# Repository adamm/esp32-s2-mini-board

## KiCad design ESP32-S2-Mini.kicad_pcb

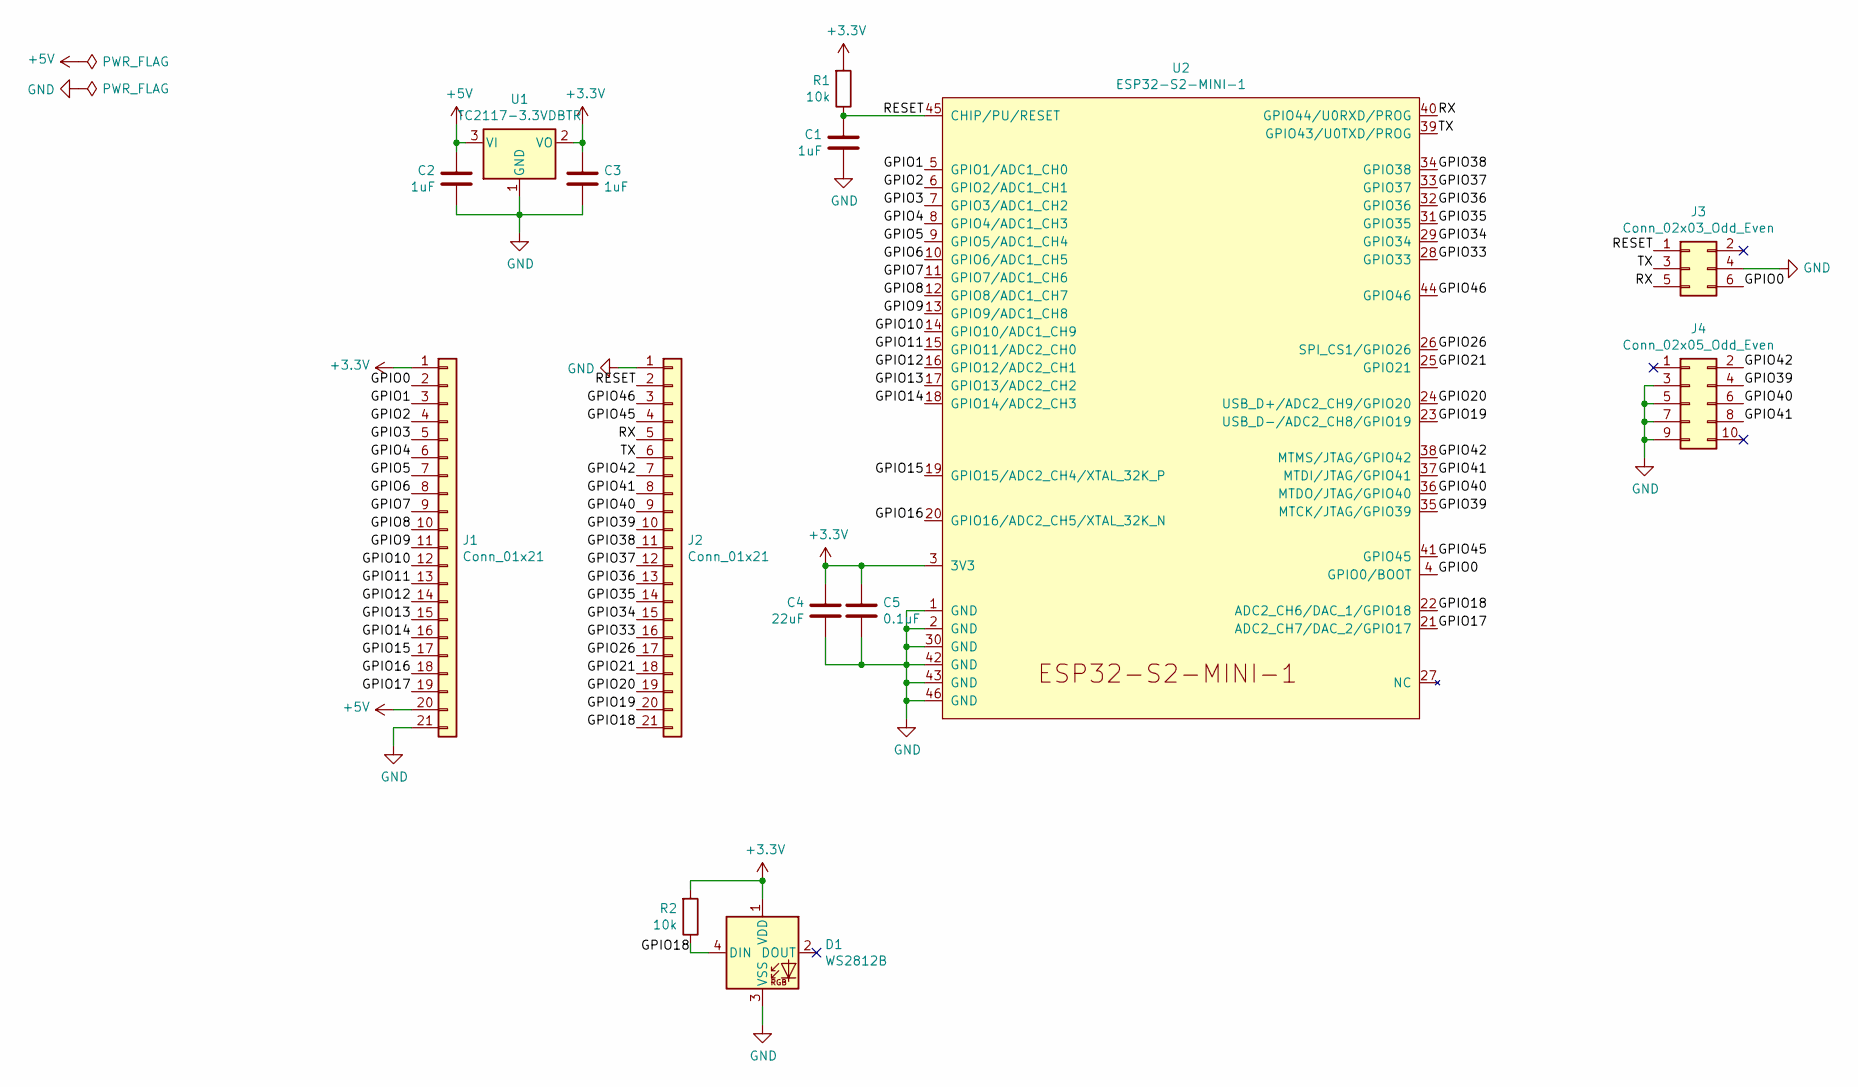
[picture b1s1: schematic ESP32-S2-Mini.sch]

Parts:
C1, C2, C3: 1uF; C_0805_2012Metric
C4: 22uF; C_0805_2012Metric
C5: 0.1uF; C_0805_2012Metric
D1: WS2812B; LED_WS2812B_PLCC4_5.0x5.0mm_P3.2mm
J1, J2: Conn_01x21; PinHeader_1x21_P2.54mm_Vertical
J3: Conn_02x03_Odd_Even; IDC-Header_2x03_P2.54mm_Vertical
J4: Conn_02x05_Odd_Even; IDC-Header_2x05_P2.54mm_Vertical
R1, R2: 10k; R_0805_2012Metric
U1: TC2117-3.3VDBTR; SOT-223-3_TabPin2
U2: ESP32-S2-MINI-1

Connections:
+3V3: C3.1, C4.2, C5.1, D1.1 (VDD), J1.1, R1.2, R2.2, U1.2 (VO), U2.3 (3V3)
+5V: C2.2, J1.20, U1.3 (VI)
/GPIO0: J1.2, J3.6, U2.4 (GPIO0/BOOT)
/GPIO1: J1.3, U2.5 (GPIO1/ADC1_CH0)
/GPIO2: J1.4, U2.6 (GPIO2/ADC1_CH1)
/GPIO3: J1.5, U2.7 (GPIO3/ADC1_CH2)
/GPIO4: J1.6, U2.8 (GPIO4/ADC1_CH3)
/GPIO5: J1.7, U2.9 (GPIO5/ADC1_CH4)
/GPIO6: J1.8, U2.10 (GPIO6/ADC1_CH5)
/GPIO7: J1.9, U2.11 (GPIO7/ADC1_CH6)
/GPIO8: J1.10, U2.12 (GPIO8/ADC1_CH7)
/GPIO9: J1.11, U2.13 (GPIO9/ADC1_CH8)
/GPIO10: J1.12, U2.14 (GPIO10/ADC1_CH9)
/GPIO11: J1.13, U2.15 (GPIO11/ADC2_CH0)
/GPIO12: J1.14, U2.16 (GPIO12/ADC2_CH1)
/GPIO13: J1.15, U2.17 (GPIO13/ADC2_CH2)
/GPIO14: J1.16, U2.18 (GPIO14/ADC2_CH3)
/GPIO15: J1.17, U2.19 (GPIO15/ADC2_CH4/XTAL_32K_P)
/GPIO16: J1.18, U2.20 (GPIO16/ADC2_CH5/XTAL_32K_N)
/GPIO17: J1.19, U2.21 (ADC2_CH7/DAC_2/GPIO17)
/GPIO18: D1.4 (DIN), J2.21, R2.1, U2.22 (ADC2_CH6/DAC_1/GPIO18)
/GPIO19: J2.20, U2.23 (USB_D-/ADC2_CH8/GPIO19)
/GPIO20: J2.19, U2.24 (USB_D+/ADC2_CH9/GPIO20)
/GPIO21: J2.18, U2.25 (GPIO21)
/GPIO26: J2.17, U2.26 (SPI_CS1/GPIO26)
/GPIO33: J2.16, U2.28 (GPIO33)
/GPIO34: J2.15, U2.29 (GPIO34)
/GPIO35: J2.14, U2.31 (GPIO35)
/GPIO36: J2.13, U2.32 (GPIO36)
/GPIO37: J2.12, U2.33 (GPIO37)
/GPIO38: J2.11, U2.34 (GPIO38)
/GPIO39: J2.10, J4.4, U2.35 (MTCK/JTAG/GPIO39)
/GPIO40: J2.9, J4.6, U2.36 (MTDO/JTAG/GPIO40)
/GPIO41: J2.8, J4.8, U2.37 (MTDI/JTAG/GPIO41)
/GPIO42: J2.7, J4.2, U2.38 (MTMS/JTAG/GPIO42)
/GPIO45: J2.4, U2.41 (GPIO45)
/GPIO46: J2.3, U2.44 (GPIO46)
/RESET: C1.2, J2.2, J3.1, R1.1, U2.45 (CHIP/PU/RESET)
/RX: J2.5, J3.5, U2.40 (GPIO44/U0RXD/PROG)
/TX: J2.6, J3.3, U2.39 (GPIO43/U0TXD/PROG)
GND: C1.1, C2.1, C3.2, C4.1, C5.2, D1.3 (VSS), J1.21, J2.1, J3.4, J4.3, J4.5, J4.7, J4.9, U1.1 (GND), U2.1 (GND), U2.2 (GND), U2.30 (GND), U2.42 (GND), U2.43 (GND), U2.46 (GND)

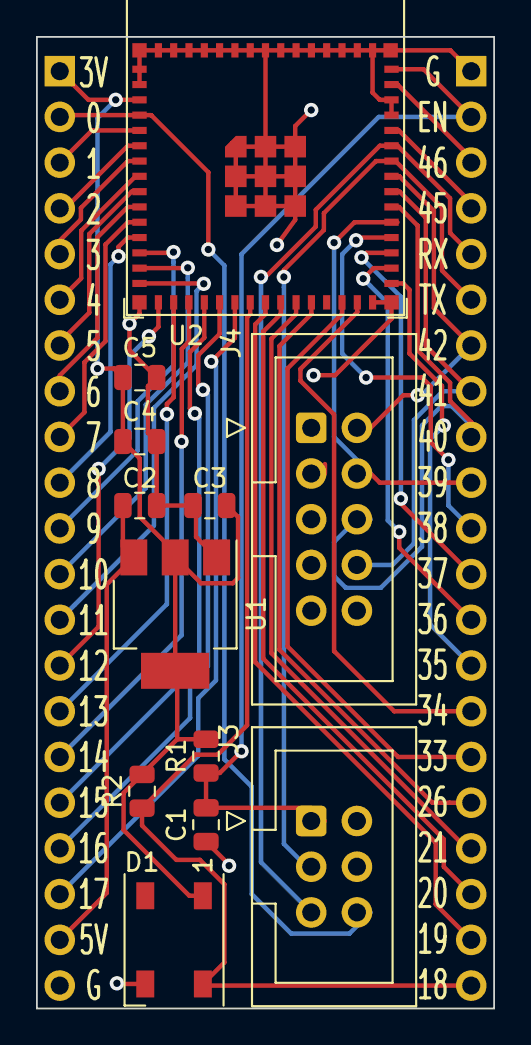
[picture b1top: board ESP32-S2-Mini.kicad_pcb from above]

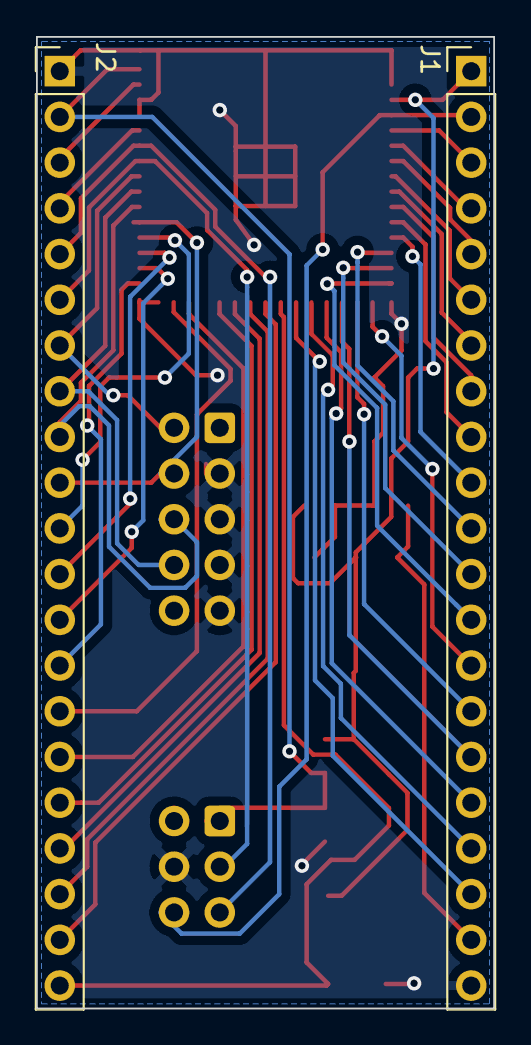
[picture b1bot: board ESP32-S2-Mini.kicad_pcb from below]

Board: 2 copper layers, 25.4 x 54.0 mm, 14 parts (2 on the bottom side), 41 nets.

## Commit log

2021-10-14 Initial commit of esp32-s2-mini custom board
2021-10-14 Added espressif kicad library as submodule
2021-10-14 Removed zip of gerber/ directory :P
2021-10-14 Ignore kicad backup files
2021-10-14 Reroute rx/tx inside the board
2021-10-14 Shrink the board slightly to fit better on a breadboard
2021-10-15 Fixed labels on right 21-pin connector block
